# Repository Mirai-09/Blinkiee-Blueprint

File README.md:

# Blinkiee-Blueprint
This is Blinkiee, a PCB that I made using a guide on Blueprint, A YSWS from Hack Club!  
# Schematic!<br>
  <br>
# PCB!
Front:  <br>
   
 <br>

Back:  <br>
  
 <br>

3D!:<br>
  
<br>

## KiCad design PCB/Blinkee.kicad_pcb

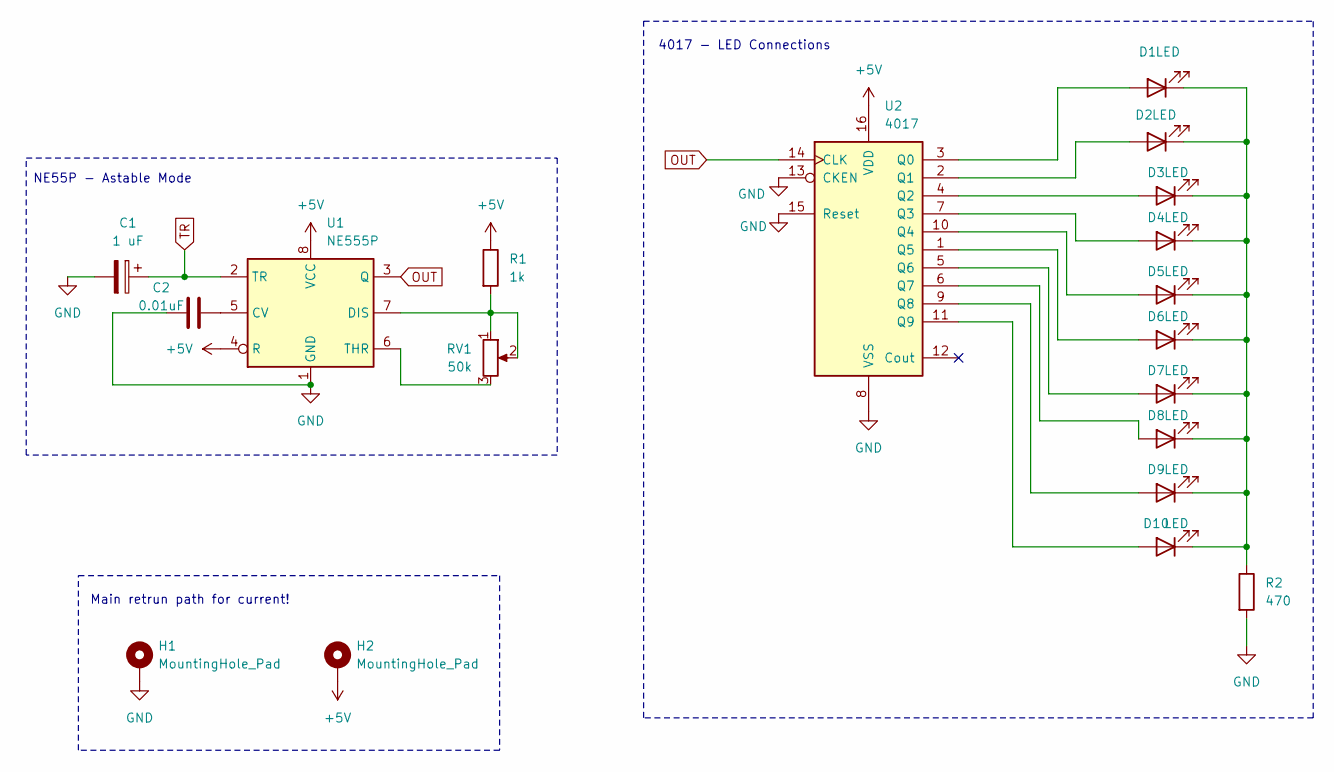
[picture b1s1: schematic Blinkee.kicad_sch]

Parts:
C1: 1 uF; CP_Radial_D5.0mm_P2.00mm
C2: 0.01uF; CP_Radial_D5.0mm_P2.00mm
D1, D2, D3, D4, D5, D6, D7, D8, D9, D10: LED; LED_D3.0mm
H1, H2: MountingHole_Pad; PinSocket_1x01_P2.54mm_Vertical
R1: 1k; R_Axial_DIN0207_L6.3mm_D2.5mm_P7.62mm_Horizontal
R2: 470; R_Axial_DIN0207_L6.3mm_D2.5mm_P7.62mm_Horizontal
RV1: 50k; Potentiometer_Vishay_T93YA_Vertical
U1: NE555P; DIP-8_W7.62mm
U2: 4017; N16

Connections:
+5V: H2.1, R1.1, U1.4 (R), U1.8 (VCC), U2.16 (VDD)
GND: C1.2, C2.1, H1.1, R2.2, U1.1 (GND), U2.8 (VSS), U2.13 (CKEN), U2.15 (Reset)
unnamed: D1.2 (A), U2.3 (Q0)
unnamed: D1.1 (K), D2.1 (K), D3.1 (K), D4.1 (K), D5.1 (K), D6.1 (K), D7.1 (K), D8.1 (K), D9.1 (K), D10.1 (K), R2.1
unnamed: D2.2 (A), U2.2 (Q1)
unnamed: D3.2 (A), U2.4 (Q2)
unnamed: D4.2 (A), U2.7 (Q3)
unnamed: D5.2 (A), U2.10 (Q4)
unnamed: D6.2 (A), U2.1 (Q5)
unnamed: D7.2 (A), U2.5 (Q6)
unnamed: D8.2 (A), U2.6 (Q7)
unnamed: D9.2 (A), U2.9 (Q8)
unnamed: D10.2 (A), U2.11 (Q9)
unnamed: C2.2, U1.5 (CV)
unnamed: R1.2, RV1.1, RV1.2, U1.7 (DIS)
unnamed: RV1.3, U1.6 (THR)
OUT: U1.3 (Q), U2.14 (CLK)
TR: C1.1, U1.2 (TR)

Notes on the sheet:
NE55P - Astable Mode
4017 - LED Connections
Main retrun path for current!

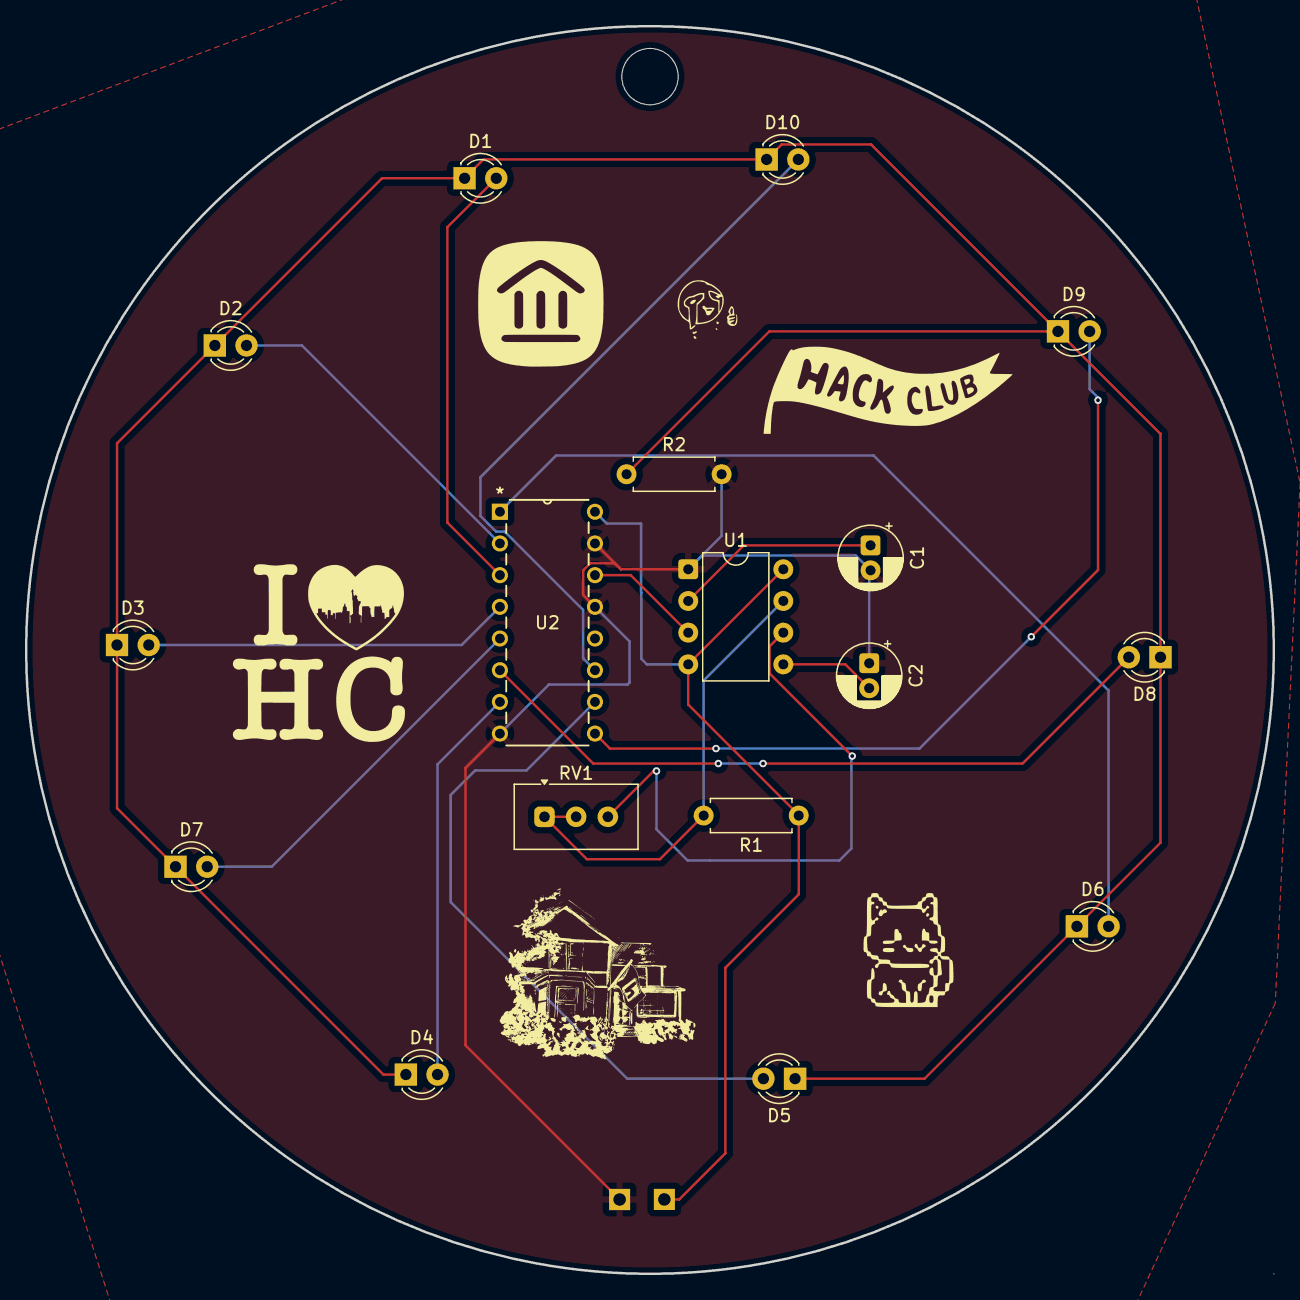
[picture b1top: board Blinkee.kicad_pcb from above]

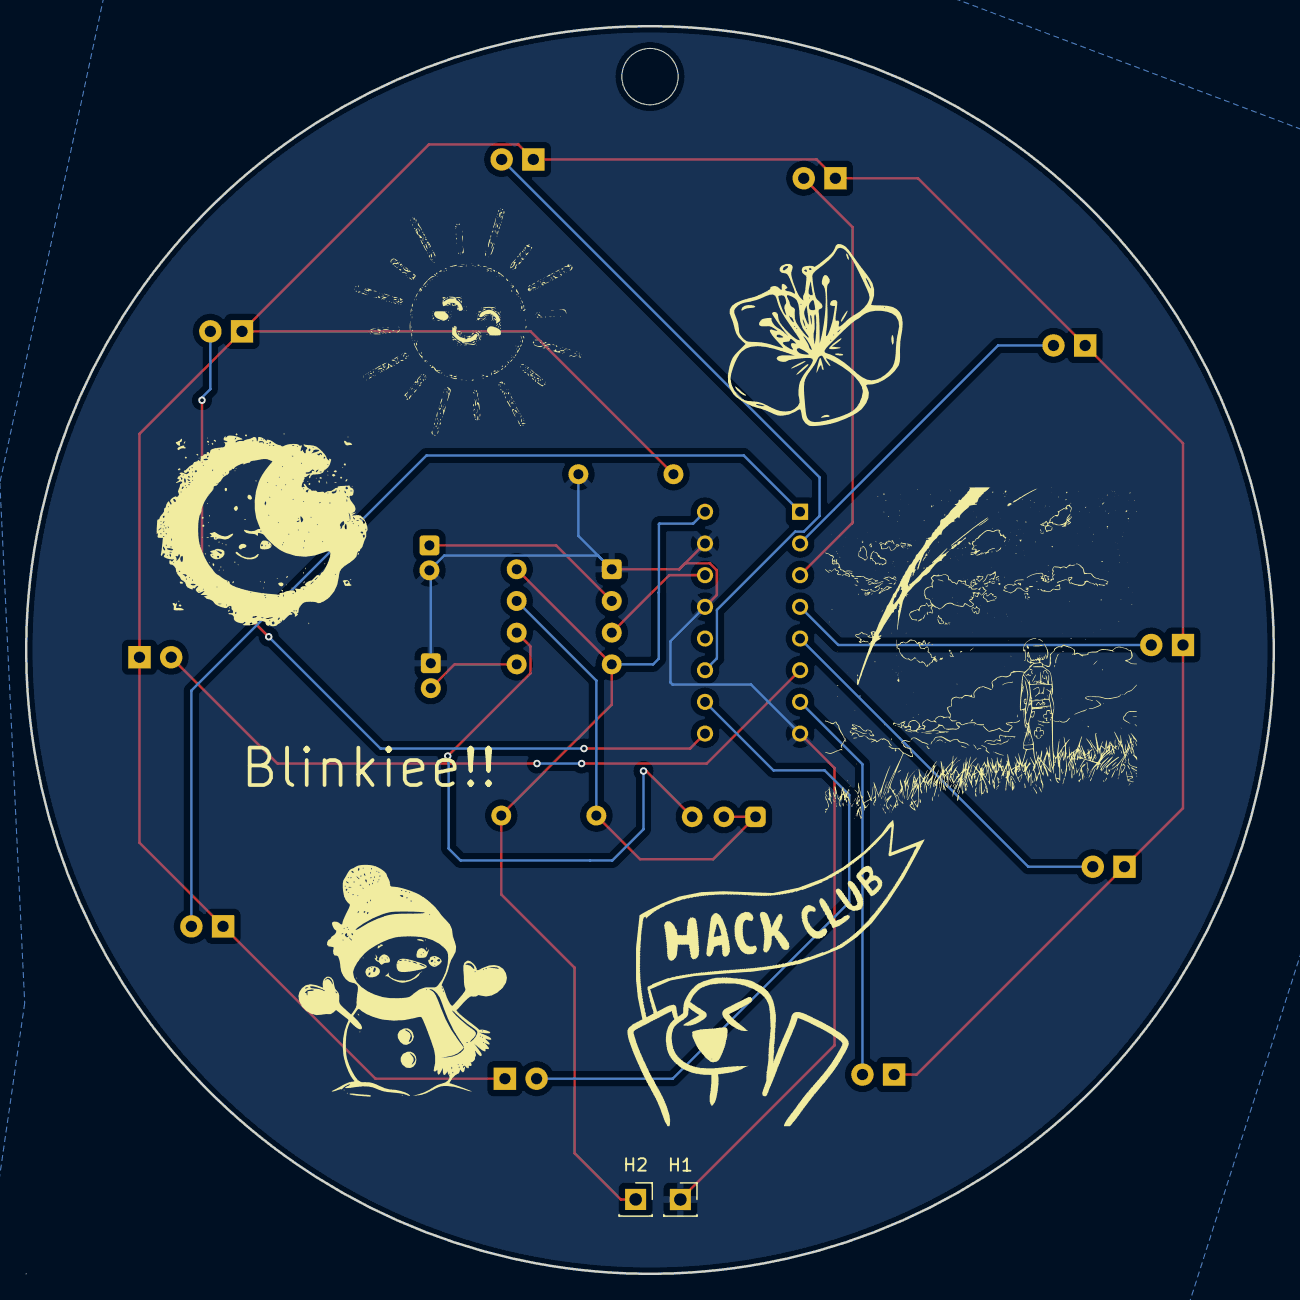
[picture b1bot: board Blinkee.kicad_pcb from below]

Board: 2 copper layers, 100.0 x 100.0 mm, 26 parts (5 on the bottom side), 18 nets.

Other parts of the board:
 : LOGO
 #2,  #3,  #4,  #5,  #6,  #7: LOGO

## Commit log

2026-03-17 Adding PCB files!
2026-04-05 Update README.md
    added <br>
